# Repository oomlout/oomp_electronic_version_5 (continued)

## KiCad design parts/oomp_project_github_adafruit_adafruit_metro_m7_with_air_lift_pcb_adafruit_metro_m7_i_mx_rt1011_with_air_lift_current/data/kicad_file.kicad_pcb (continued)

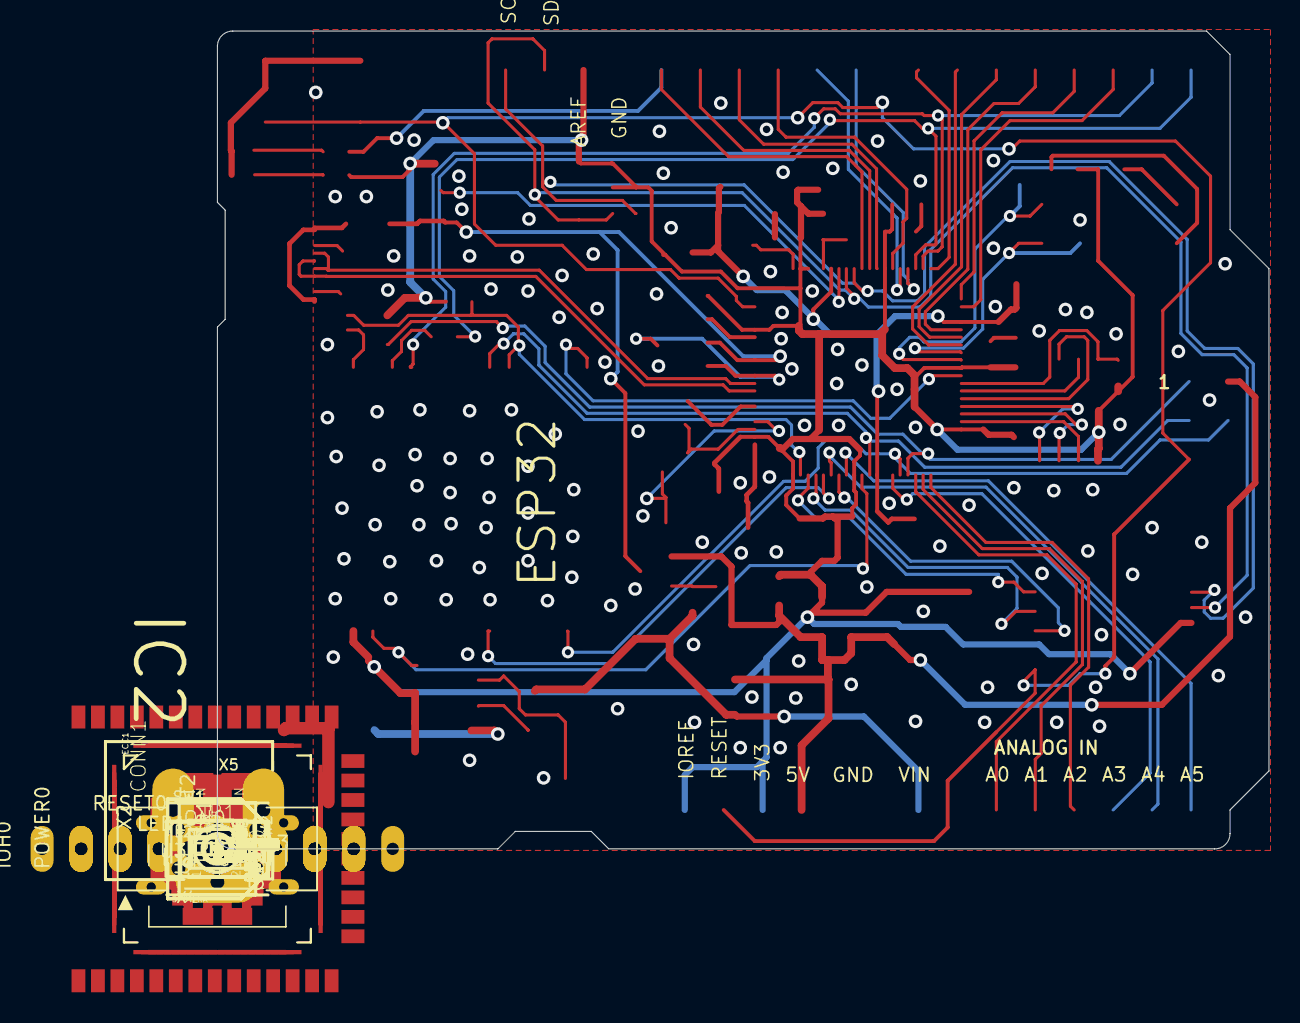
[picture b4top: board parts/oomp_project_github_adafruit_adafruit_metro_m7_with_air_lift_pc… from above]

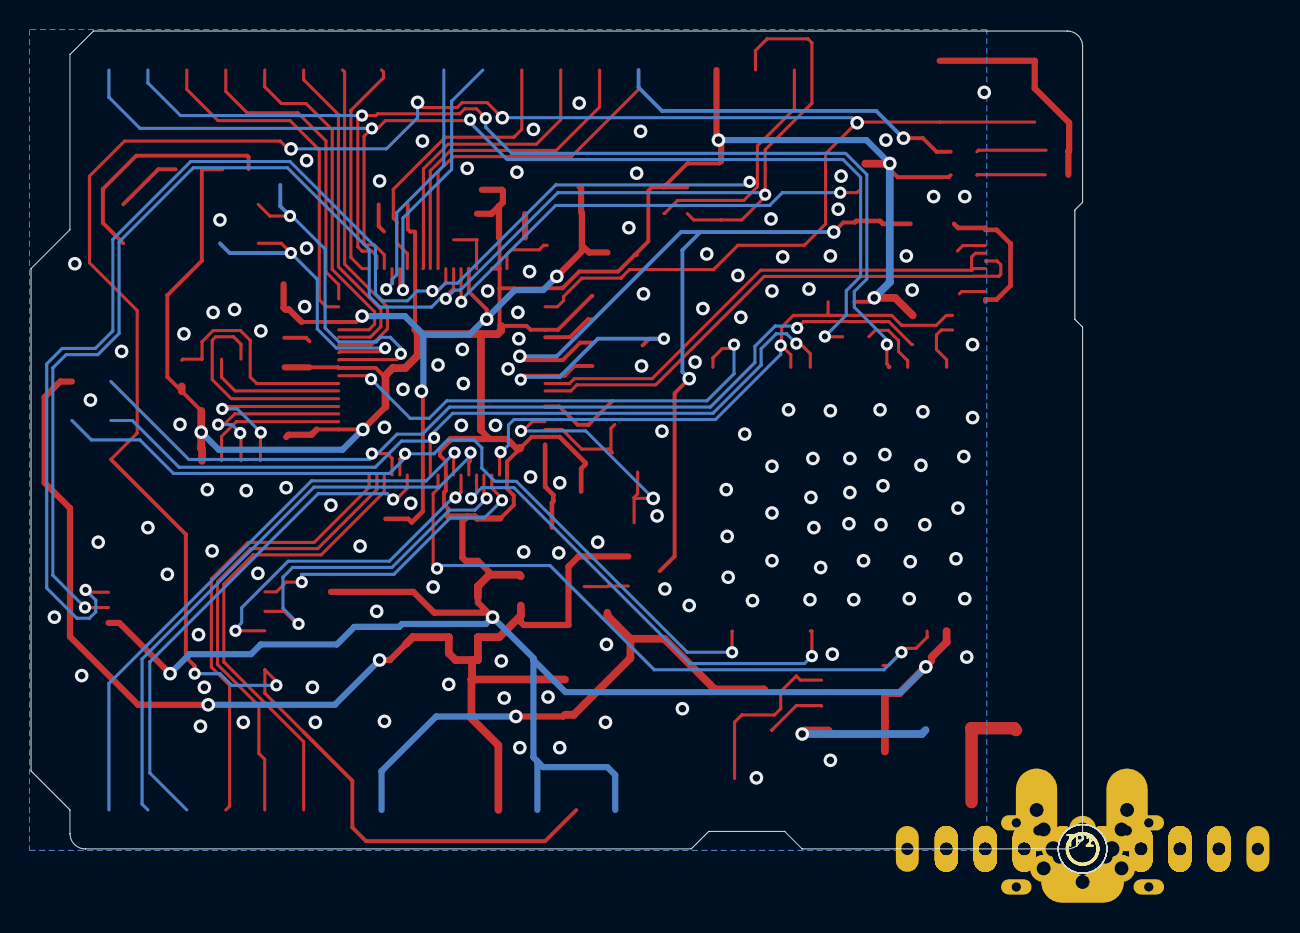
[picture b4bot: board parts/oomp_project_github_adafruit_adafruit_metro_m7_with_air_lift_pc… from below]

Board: 2 copper layers, 68.6 x 53.3 mm, 105 parts (3 on the bottom side), 71 nets.

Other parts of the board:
U$11: PCBFEAT-REV-040
U$12: METROM7_RT1011AIR_BOT
U$18: METROM7_RT1011AIR_TOP
UNK_HOLE_0: dummyfp0
UNK_HOLE_1: dummyfp1
UNK_HOLE_2: dummyfp2
UNK_HOLE_3: dummyfp3

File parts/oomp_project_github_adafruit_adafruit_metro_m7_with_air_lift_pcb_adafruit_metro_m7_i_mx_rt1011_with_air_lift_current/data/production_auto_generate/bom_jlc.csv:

Comment,Designator,Footprint,LCSC Part #
,JP1,Adafruit Metro M7 iMX RT1011 with AirLift-import-fps:1X01_ROUND,C7501259
,U$12,Adafruit Metro M7 iMX RT1011 with AirLift-import-fps:METROM7_RT1011AIR_BOT,
,U$18,Adafruit Metro M7 iMX RT1011 with AirLift-import-fps:METROM7_RT1011AIR_TOP,
,U$11,Adafruit Metro M7 iMX RT1011 with AirLift-import-fps:PCBFEAT-REV-040,
,"TP1,TP2",Adafruit Metro M7 iMX RT1011 with AirLift-import-fps:TESTPOINT_ROUND_1.5MM,
0.1uF,"C6,C7,C12,C13,C22,C32,C35,C37,C41,C43",Adafruit Metro M7 iMX RT1011 with AirLift-import-fps:0603-NO,C14663
0.22uF,"C33,C38,C49,C50,C52,C53,C56,C57,C58",Adafruit Metro M7 iMX RT1011 with AirLift-import-fps:0603-NO,
100K,"R1,R16",Adafruit Metro M7 iMX RT1011 with AirLift-import-fps:0603-NO,C25803
10K,"R5,R7,R9,R10,R12,R13,R15",Adafruit Metro M7 iMX RT1011 with AirLift-import-fps:0603-NO,C98220
10uF,"C2,C3,C5,C18,C19,C20,C21,C31,C39,C40,C45,C46,C47,C48,C51,C55",Adafruit Metro M7 iMX RT1011 with AirLift-import-fps:0805-NO,
16pF,"C25,C26",Adafruit Metro M7 iMX RT1011 with AirLift-import-fps:0603-NO,
1uF,"C29,C30,C36,C42,C44,C54",Adafruit Metro M7 iMX RT1011 with AirLift-import-fps:0603-NO,C5673
1x10F,IOH0,Adafruit Metro M7 iMX RT1011 with AirLift-import-fps:1X10_OVALWAVE,C57369
1x6F,AD0,Adafruit Metro M7 iMX RT1011 with AirLift-import-fps:1X06_OVALWAVE,C37208
1x8F,"IOL0,POWER0",Adafruit Metro M7 iMX RT1011 with AirLift-import-fps:1X08_OVALWAVE,C492421
2.1mm,X5,Adafruit Metro M7 iMX RT1011 with AirLift-import-fps:DCJACK_2MM_PTH,
2.2M,R4,Adafruit Metro M7 iMX RT1011 with AirLift-import-fps:0603-NO,C2933170
22uF,C34,Adafruit Metro M7 iMX RT1011 with AirLift-import-fps:0805-NO,
24MHz 10pF,Y1,Adafruit Metro M7 iMX RT1011 with AirLift-import-fps:CRYSTAL_2.5X2,
2x3M,ICSP0,Adafruit Metro M7 iMX RT1011 with AirLift-import-fps:2X03_ROUND_70MIL,
"2x5 0.05"" SWD",X2,Adafruit Metro M7 iMX RT1011 with AirLift-import-fps:2X05_1.27MM_BOX_POSTS,
30K,R6,Adafruit Metro M7 iMX RT1011 with AirLift-import-fps:0603-NO,
4.7uH,L2,Adafruit Metro M7 iMX RT1011 with AirLift-import-fps:INDUCTOR_1007,
47uF/25V,"PC1,PC2",Adafruit Metro M7 iMX RT1011 with AirLift-import-fps:PANASONIC_D,
5.1K,"R2,R3,R8,R11,R14,R17",Adafruit Metro M7 iMX RT1011 with AirLift-import-fps:0603-NO,C23186
6x6mm,RESET0,Adafruit Metro M7 iMX RT1011 with AirLift-import-fps:EVQ-Q2_SMALLER,
74AHC1G125,IC1,Adafruit Metro M7 iMX RT1011 with AirLift-import-fps:SOT23-5L,
AP2112K-3.3,U2,Adafruit Metro M7 iMX RT1011 with AirLift-import-fps:SOT23-DBV,
ATECC108,ECC1,Adafruit Metro M7 iMX RT1011 with AirLift-import-fps:SOIC8,
DIP2,SW2,Adafruit Metro M7 iMX RT1011 with AirLift-import-fps:DIPSWITCH_2PIN,
DMP3098L-7,"T2,TR1",Adafruit Metro M7 iMX RT1011 with AirLift-import-fps:SOT-23,
ESP32_WROOM32,X6,Adafruit Metro M7 iMX RT1011 with AirLift-import-fps:WROOM32,
FIDUCIAL_1MM,"FD1,FD2,FD3",Adafruit Metro M7 iMX RT1011 with AirLift-import-fps:FIDUCIAL_1MM,
FUSE,F2,Adafruit Metro M7 iMX RT1011 with AirLift-import-fps:R1206,
GREEN,ON0,Adafruit Metro M7 iMX RT1011 with AirLift-import-fps:CHIPLED_0603_NOOUTLINE,
IMX_RT1010,IC2,Adafruit Metro M7 iMX RT1011 with AirLift-import-fps:QFP50P1400X1400X160-80N,
MBR120,D1,Adafruit Metro M7 iMX RT1011 with AirLift-import-fps:SOD-123,
NCP1117ST50T3G,U1,Adafruit Metro M7 iMX RT1011 with AirLift-import-fps:SOT223-R,
RED,L0,Adafruit Metro M7 iMX RT1011 with AirLift-import-fps:CHIPLED_0603_NOOUTLINE,
RESET_SUPERVISORAPX80X_SA,IC4,Adafruit Metro M7 iMX RT1011 with AirLift-import-fps:SOT23-WIDE,
SPDT_RA,SW1,Adafruit Metro M7 iMX RT1011 with AirLift-import-fps:SPDT_SMT_SSSS811101,
STEMMA_I2C_QT,CONN1,Adafruit Metro M7 iMX RT1011 with AirLift-import-fps:JST_SH4,C160404
USB C,X4,Adafruit Metro M7 iMX RT1011 with AirLift-import-fps:USB_C_CUSB31-CFM2AX-01-X,
W25Q64JV,U3,Adafruit Metro M7 iMX RT1011 with AirLift-import-fps:SOIC8_208MIL,
WS2812B_3535FULL,LED1,Adafruit Metro M7 iMX RT1011 with AirLift-import-fps:LED3535_FULLPADS,
